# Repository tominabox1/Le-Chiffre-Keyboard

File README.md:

# Le Chiffre (ironically, "the number" in French)
The purpose of the board is to provide a platform for MX and Choc ergo (Alps support too!) in one package for when ones wrists need a break. The board supports an RGB LED strip with DI on port F0. The board is also fitted with support for run-of-the-mill .91" OLED and EC11 rotary encoder.

Great thanks goes to Jake at P3D for really making the case amazing and open sourcing his work. Check him out at P3Dstore.com

Firmware for the keyboard is available here: https://github.com/qmk/qmk_firmware/tree/master/keyboards/tominabox1/le_chiffre

This project is open sourced with the GPL-3.0 license. The license conditionally allows for commercial use, modification, distribution, patent, and private use. Please take note of the license conditions before utilizing this project. 

## Bill of materials
You can copy this table when ordering PCBs. 
| Item # | *Ref Des                                                                                                                                                             | *Qty | *Mfg Part #        | Description\Value | *Package         |
|--------|----------------------------------------------------------------------------------------------------------------------------------------------------------------------|------|--------------------|-------------------|------------------|
| 1      | D1, D2, D3, D4, D5, D6, D7, D8, D9, D10, D11, D12, D13, D14, D15, D16, D17, D18, D19, D20, D21, D22, D23, D24, D25, D26, D27, D28, D29, D30, D31, D32, D33, D34, D35 | 35   | 1N4148W            |                   | SOD-123          |
| 2      | R7, R8                                                                                                                                                               | 2    | 0603WAF4701T5E     | 4.7k              | 0805             |
| 3      | R6, R5                                                                                                                                                               | 2    | 0805W8F1002T5E     | 10k               | 0805             |
| 4      | R4, R3                                                                                                                                                               | 2    | 0805W8F220JT5E     | 22r               | 0805             |
| 5      | R2, R1                                                                                                                                                               | 2    | 0805W8F5101T5E     | 5.1k              | 0805             |
| 6      | SW1                                                                                                                                                                  | 1    | TS-1076S-A1B2      | SW_Push           | SMD,5.2x5.2x1.5  |
| 7      | F1                                                                                                                                                                   | 1    | SMD0805-020        |                   | 0805             |
| 8      | C8                                                                                                                                                                   | 1    | GRM188R60J475KE19D | 4.7uF             | 0603             |
| 9      | C7, C5, C2, C1                                                                                                                                                       | 4    | GRM188R71H104KA93D | 0.1uF             | 0603             |
| 10     | C6, C3                                                                                                                                                               | 2    | GRM1882C1H220JA01D | 22pf              | 0603             |
| 11     | C4                                                                                                                                                                   | 1    | CC0603KRX5R6BB105  | 1uF               | 0603             |
| 12     | Y1                                                                                                                                                                   | 1    | X322516MLB4SI      | 16MHz             | 3.2x2.5mm, 4 pad |
| 13     | U1                                                                                                                                                                   | 1    | ATMEGA32U4-AU      |                   | 44-TQFP          |
| 14     | USB1                                                                                                                                                                 | 1    | TYPE-C-31-M-12     |                   |                  |
| 15     | D111, D110, D109, D108, D107, D106, D105, D104, D103, D102, D101                                                                                                     | 11   | WS2812B-B          |                   | LED-4_5050       |

# Fab files
If you just want to order PCBs and plates, just grab these files and send them to your fab house. Also include the BOM from above.

[PCB](KiCad/Le%20Chiffre%20v2/Fab/PCB/LeChiffrePCBFab.zip)

[Plate](KiCad/Le%20Chiffre%20v2/Fab/Plate/LeChiffrePlateFab.zip) (this is for one side, order 2 for each PCB)

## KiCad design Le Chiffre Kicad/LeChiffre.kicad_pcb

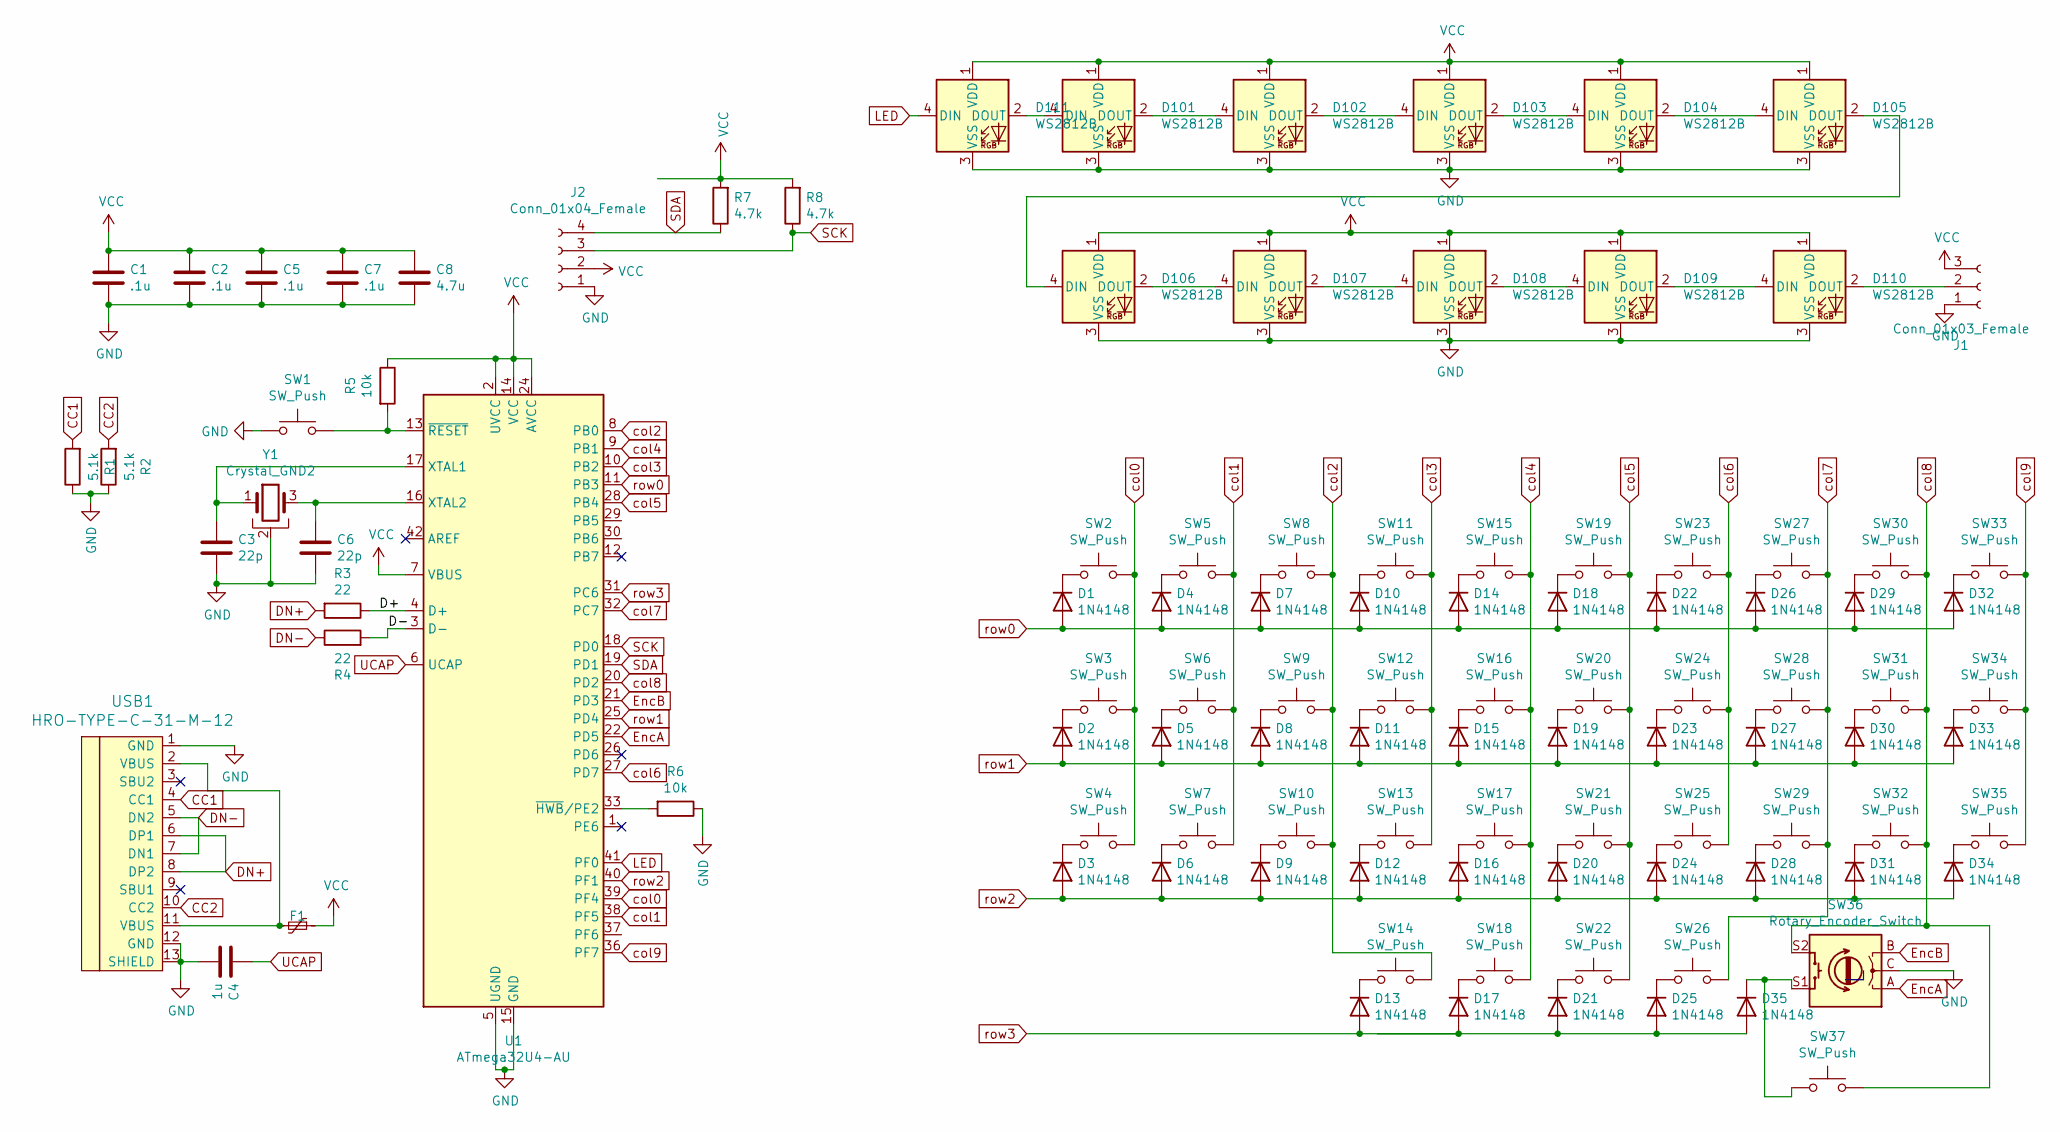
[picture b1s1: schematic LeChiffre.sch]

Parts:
C1, C2, C5, C7: .1u; C_0603
C3, C6: 22p; C_0603
C4: 1u; C_0603
C8: 4.7u; C_0603
D1, D2, D3, D4, D5, D6, D7, D8, D9, D10, D11, D12, D13, D14, D15, D16, D17, D18, D19, D20, D21, D22, D23, D24, D25, D26, D27, D28, D29, D30, D31, D32, D33, D34, D35: 1N4148; D_SOD123
D101, D102, D103, D104, D105, D106, D107, D108, D109, D110, D111: WS2812B; LED_WS2812B_PLCC4_5.0x5.0mm_P3.2mm
F1: Polyfuse_Small; Fuse_0805
J1: Conn_01x03_Female; PinSocket_1x03_P2.54mm_Vertical
J2: Conn_01x04_Female; PinSocket_1x04_P2.54mm_Vertical
R1, R2: 5.1k; R_0805
R3, R4: 22; R_0805
R5, R6: 10k; R_0805
R7, R8: 4.7k; R_0805
SW1: SW_Push; SW_SPST_TL3342
SW2, SW3, SW4, SW5, SW6, SW7, SW8, SW9, SW10, SW11, SW12, SW13, SW14, SW15, SW16, SW17, SW19, SW20, SW21, SW23, SW24, SW25, SW26, SW27, SW28, SW29, SW30, SW31, SW32, SW33, SW34, SW35, SW37: SW_Push; MX-Alps-Choc-1U-NoLED
SW18, SW22: SW_Push; MX-Alps-Choc-2U-StabFlip
SW36: Rotary_Encoder_Switch; RotaryEncoder_Alps_EC12E-Switch_Vertical_H20mm_CircularMoun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
U1: ATmega32U4-AU; ATMEGA32U4-AU
USB1: HRO-TYPE-C-31-M-12; HRO-TYPE-C-31-M-12-HandSoldering
Y1: Crystal_GND2; Crystal_SMD_3225-4pin_3.2x2.5mm

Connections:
/D+: R3.1, U1.4 (D+)
/D-: R4.2, U1.3 (D-)
CC1: R1.2, USB1.4 (CC1)
CC2: R2.2, USB1.10 (CC2)
DN+: R3.2, USB1.6 (DP1), USB1.8 (DP2)
DN-: R4.1, USB1.5 (DN2), USB1.7 (DN1)
EncA: SW36.A, U1.22 (PD5)
EncB: SW36.B, U1.21 (PD3)
GND: C1.2, C2.2, C3.2, C4.2, C5.2, C6.2, C7.2, C8.2, D101.3 (VSS), D102.3 (VSS), D103.3 (VSS), D104.3 (VSS), D105.3 (VSS), D106.3 (VSS), D107.3 (VSS), D108.3 (VSS), D109.3 (VSS), D110.3 (VSS), D111.3 (VSS), J1.1 (Pin_3), J2.1, R1.1, R2.1, R6.1, SW1.1, SW36.C, U1.5 (UGND), U1.15 (GND), U1.23 (GND), U1.35 (GND), U1.43 (GND), USB1.1 (GND), USB1.12 (GND), USB1.13 (SHIELD), Y1.2
LED: D111.4 (DIN), U1.41 (PF0)
unnamed: C3.1, U1.17 (XTAL1), Y1.1
unnamed: C6.1, U1.16 (XTAL2), Y1.3
unnamed: D1.1 (K), SW2.1
unnamed: D2.1 (K), SW3.1
unnamed: D3.1 (K), SW4.1
unnamed: D4.1 (K), SW5.1
unnamed: D5.1 (K), SW6.1
unnamed: D6.1 (K), SW7.1
unnamed: D7.1 (K), SW8.1
unnamed: D8.1 (K), SW9.1
unnamed: D9.1 (K), SW10.1
unnamed: D10.1 (K), SW11.1
unnamed: D11.1 (K), SW12.1
unnamed: D12.1 (K), SW13.1
unnamed: D13.1 (K), SW14.1
unnamed: D14.1 (K), SW15.1
unnamed: D15.1 (K), SW16.1
unnamed: D16.1 (K), SW17.1
unnamed: D17.1 (K), SW18.1
unnamed: D18.1 (K), SW19.1
unnamed: D19.1 (K), SW20.1
unnamed: D20.1 (K), SW21.1
unnamed: D21.1 (K), SW22.1
unnamed: D22.1 (K), SW23.1
unnamed: D23.1 (K), SW24.1
unnamed: D24.1 (K), SW25.1
unnamed: D25.1 (K), SW26.1
unnamed: D26.1 (K), SW27.1
unnamed: D27.1 (K), SW28.1
unnamed: D28.1 (K), SW29.1
unnamed: D29.1 (K), SW30.1
unnamed: D30.1 (K), SW31.1
unnamed: D31.1 (K), SW32.1
unnamed: D32.1 (K), SW33.1
unnamed: D33.1 (K), SW34.1
unnamed: D34.1 (K), SW35.1
unnamed: D35.1 (K), SW36.S1, SW37.1
unnamed: D101.2 (DOUT), D102.4 (DIN)
unnamed: D101.4 (DIN), D111.2 (DOUT)
unnamed: D102.2 (DOUT), D103.4 (DIN)
unnamed: D103.2 (DOUT), D104.4 (DIN)
unnamed: D104.2 (DOUT), D105.4 (DIN)
unnamed: D105.2 (DOUT), D106.4 (DIN)
unnamed: D106.2 (DOUT), D107.4 (DIN)
unnamed: D107.2 (DOUT), D108.4 (DIN)
unnamed: D108.2 (DOUT), D109.4 (DIN)
unnamed: D109.2 (DOUT), D110.4 (DIN)
unnamed: D110.2 (DOUT), J1.2
unnamed: F1.2, USB1.2 (VBUS), USB1.11 (VBUS)
unnamed: R5.2, SW1.2, U1.13 (~RESET)
unnamed: R6.2, U1.33 (~HWB~/PE2)
SCK: J2.3, R8.1, U1.18 (PD0)
SDA: J2.4, R7.1, U1.19 (PD1)
UCAP: C4.1, U1.6 (UCAP)
VCC: C1.1, C2.1, C5.1, C7.1, C8.1, D101.1 (VDD), D102.1 (VDD), D103.1 (VDD), D104.1 (VDD), D105.1 (VDD), D106.1 (VDD), D107.1 (VDD), D108.1 (VDD), D109.1 (VDD), D110.1 (VDD), D111.1 (VDD), F1.1, J1.3 (Pin_1), J2.2, R5.1, R7.2, R8.2, U1.2 (UVCC), U1.7 (VBUS), U1.14 (VCC), U1.24 (AVCC), U1.34 (VCC), U1.44 (AVCC)
col0: SW2.2, SW3.2, SW4.2, U1.39 (PF4)
col1: SW5.2, SW6.2, SW7.2, U1.38 (PF5)
col2: SW8.2, SW9.2, SW10.2, SW14.2, U1.8 (PB0)
col3: SW11.2, SW12.2, SW13.2, U1.10 (PB2)
col4: SW15.2, SW16.2, SW17.2, SW18.2, U1.9 (PB1)
col5: SW19.2, SW20.2, SW21.2, SW22.2, U1.28 (PB4)
col6: SW23.2, SW24.2, SW25.2, U1.27 (PD7)
col7: SW26.2, SW27.2, SW28.2, SW29.2, U1.32 (PC7)
col8: SW30.2, SW31.2, SW32.2, SW36.S2, SW37.2, U1.20 (PD2)
col9: SW33.2, SW34.2, SW35.2, U1.36 (PF7)
row0: D1.2 (A), D4.2 (A), D7.2 (A), D10.2 (A), D14.2 (A), D18.2 (A), D22.2 (A), D26.2 (A), D29.2 (A), D32.2 (A), U1.11 (PB3)
row1: D2.2 (A), D5.2 (A), D8.2 (A), D11.2 (A), D15.2 (A), D19.2 (A), D23.2 (A), D27.2 (A), D30.2 (A), D33.2 (A), U1.25 (PD4)
row2: D3.2 (A), D6.2 (A), D9.2 (A), D12.2 (A), D16.2 (A), D20.2 (A), D24.2 (A), D28.2 (A), D31.2 (A), D34.2 (A), U1.40 (PF1)
row3: D13.2 (A), D17.2 (A), D21.2 (A), D25.2 (A), D35.2 (A), U1.31 (PC6)

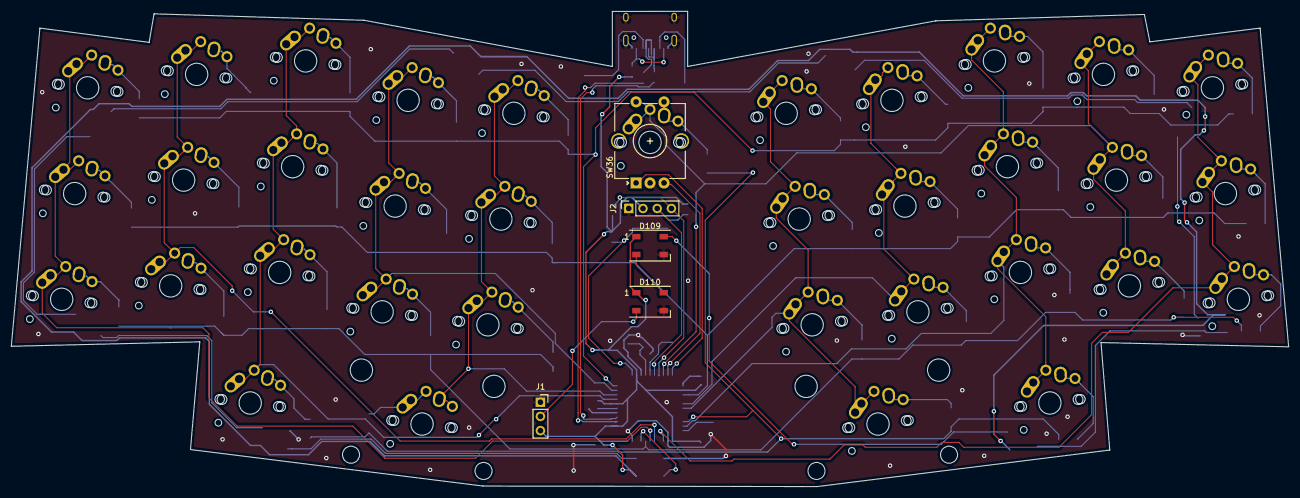
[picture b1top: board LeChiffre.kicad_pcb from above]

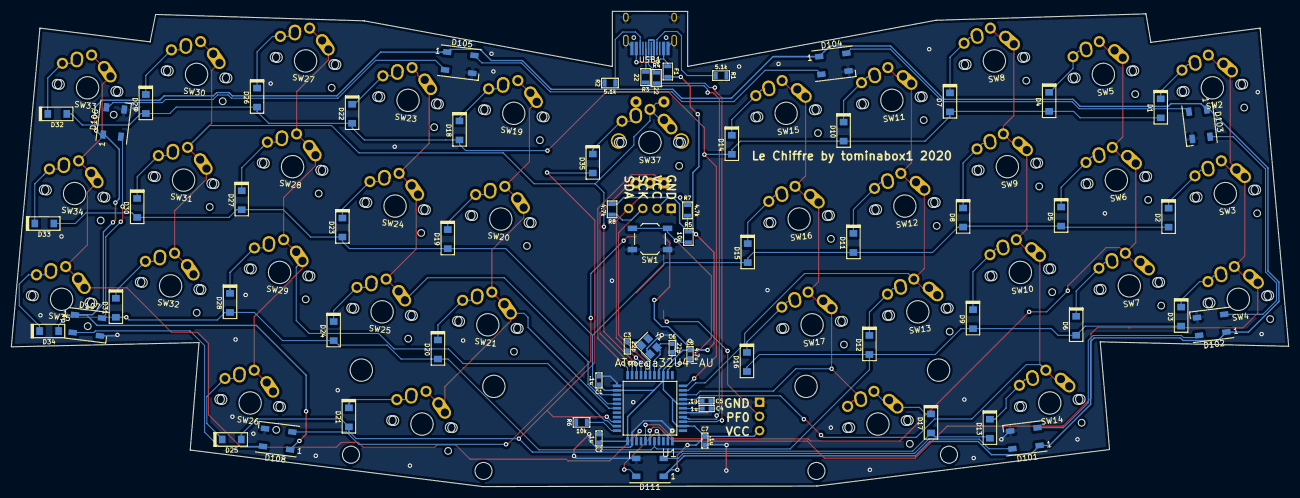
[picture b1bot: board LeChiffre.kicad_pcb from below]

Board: 2 copper layers, 228.4 x 85.0 mm, 105 parts (65 on the bottom side), 79 nets.

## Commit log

2020-05-30 Added P3D Case Mods
2020-08-11 Adding kicad project
2020-09-10 Add files via upload
    OLED bezel for P3D cases.
2020-10-28 Add latest 3DP Case with Acrylic Bottom or 3DP Bottom
2020-10-31 Rename project to Le Chiffre. Update pcb with RGB LEDs on bottom and top. Clean up layout a bit. Remove gerber folders (please generate from the kicad file)
2020-10-31 Orgaize cases
2020-10-31 Move P3D new case into cases
2020-11-04 Update PCB
2021-08-05 added the bluetooth capable drop-in replacement PCB le_chiff_ble as a git submodule
2021-08-06 Added new 3dp case
2021-08-06 reorganizing for the addition of ble submodule
2021-09-01 updated plate for room for RGB Chiffre designs
2021-09-21 Adding BOM and Gerber files
2022-01-11 fix part number errors
2022-04-29 Update README.md
    Fixed the QMK firmware link.
